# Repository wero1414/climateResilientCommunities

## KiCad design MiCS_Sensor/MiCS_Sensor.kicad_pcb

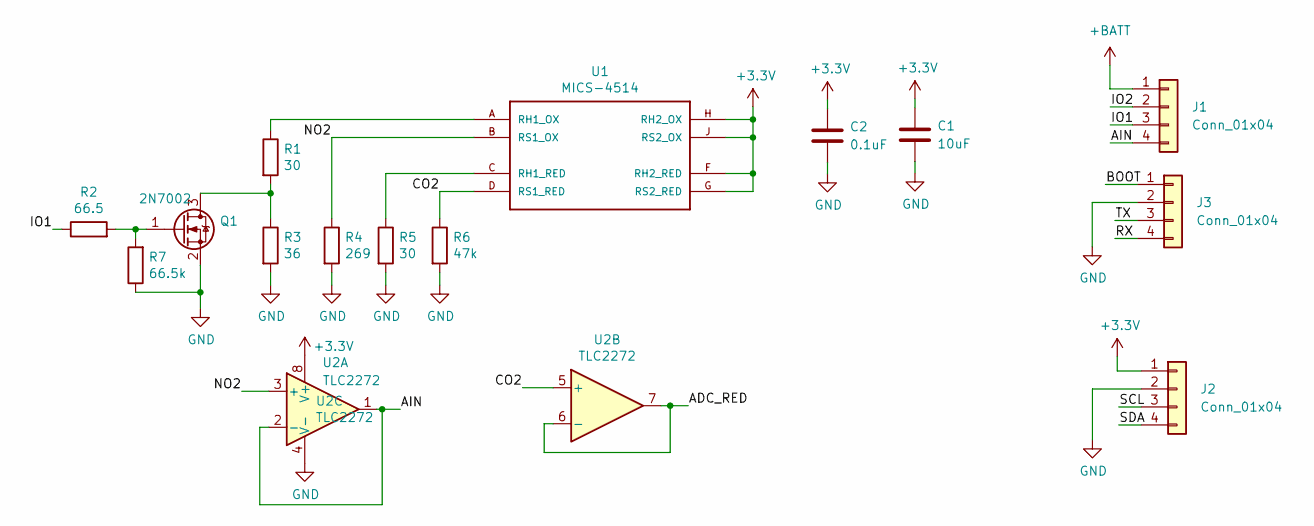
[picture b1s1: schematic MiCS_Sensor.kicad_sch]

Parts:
C1: 10uF; C_0805_2012Metric
C2: 0.1uF; C_0805_2012Metric
J1, J2, J3: Conn_01x04; PinHeader_1x04_P2.54mm_Vertical
Q1: 2N7002; SOT-23
R1, R5: 30; R_0805_2012Metric
R2: 66.5; R_0805_2012Metric
R3: 36; R_0805_2012Metric
R4: 269; R_0805_2012Metric
R6: 47k; R_0805_2012Metric
R7: 66.5k; R_0805_2012Metric
U1: MICS-4514; MICS_10-SMD
U2: TLC2272; SOIC-8_3.9x4.9mm_P1.27mm

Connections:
+3V3: C1.1, C2.1, J2.1, U1.F (RH2_RED), U1.G (RS2_RED), U1.H (RH2_OX), U1.J (RS2_OX), U2.8 (V+)
+BATT: J1.1
/ADC_RED: U2.6 (-), U2.7
/AIN: J1.4, U2.1, U2.2 (-)
/BOOT: J3.1
/CO2: R6.1, U1.D (RS1_RED), U2.5 (+)
/IO1: J1.3, R2.1
/IO2: J1.2
/NO2: R4.1, U1.B (RS1_OX), U2.3 (+)
/RX: J3.4
/SCL: J2.3
/SDA: J2.4
/TX: J3.3
GND: C1.2, C2.2, J2.2, J3.2, Q1.2 (S), R3.2, R4.2, R5.2, R6.2, R7.1, U2.4 (V-)
unnamed: Q1.1 (G), R2.2, R7.2
unnamed: Q1.3 (D), R1.2, R3.1
unnamed: R1.1, U1.A (RH1_OX)
unnamed: R5.1, U1.C (RH1_RED)

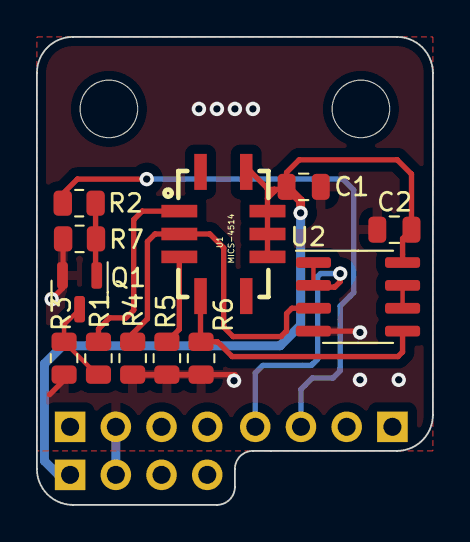
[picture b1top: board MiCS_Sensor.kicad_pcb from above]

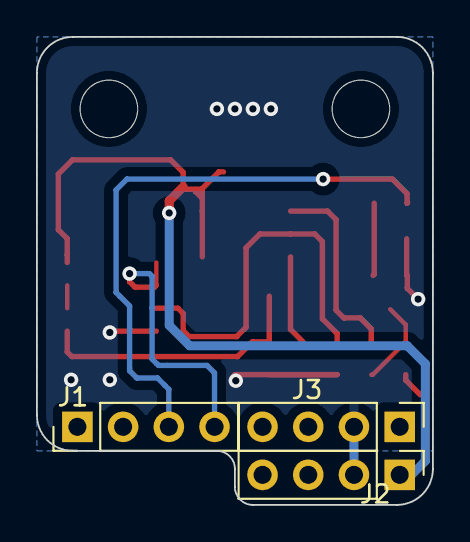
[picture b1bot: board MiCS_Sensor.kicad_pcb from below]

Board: 2 copper layers, 22.0 x 26.0 mm, 15 parts (3 on the bottom side), 11 nets.

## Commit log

2022-05-14 add kicad project missing main connections to board
2022-05-14 update 3D file
2022-05-22 update version
2022-05-22 add gerber files for sensor v1.0
2022-05-25 add fw
2022-06-11 update firmware
2022-06-15 fix voc compilation
2022-07-05 add data to send with analog
2022-07-06 Fix PPM calculation
2022-07-06 add index.js for firebase functions
2022-07-06 add json example
2022-07-06 change index
2022-07-08 clean code
2022-07-08 add gitignore for MacOS
2022-07-08 update notes on schematic
